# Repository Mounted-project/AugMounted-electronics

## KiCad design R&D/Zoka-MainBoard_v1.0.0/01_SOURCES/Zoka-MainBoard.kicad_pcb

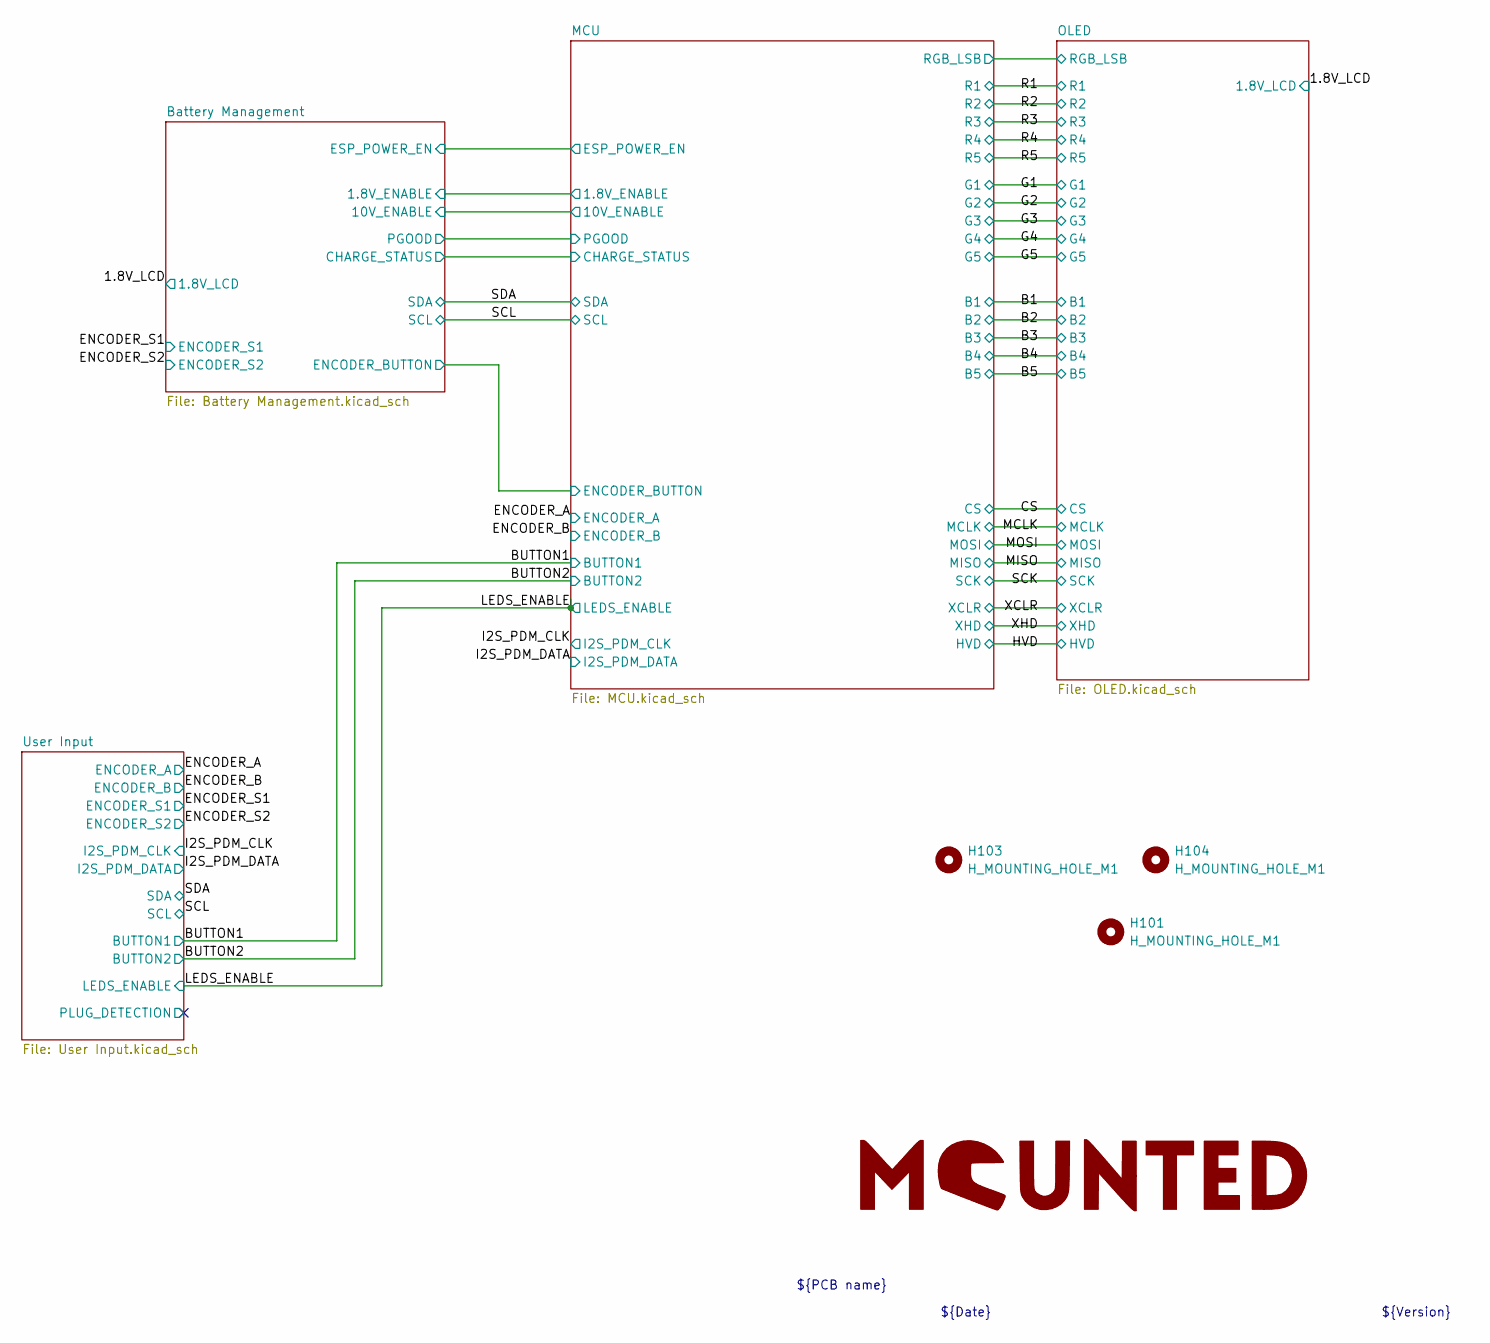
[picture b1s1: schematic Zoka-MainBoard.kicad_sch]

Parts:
H101, H103, H104: H_MOUNTING_HOLE_M1; MountingHole_1.2mm_M1
LOGO101: mounted_logo

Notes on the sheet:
${PCB name}
${Date}
${Version}

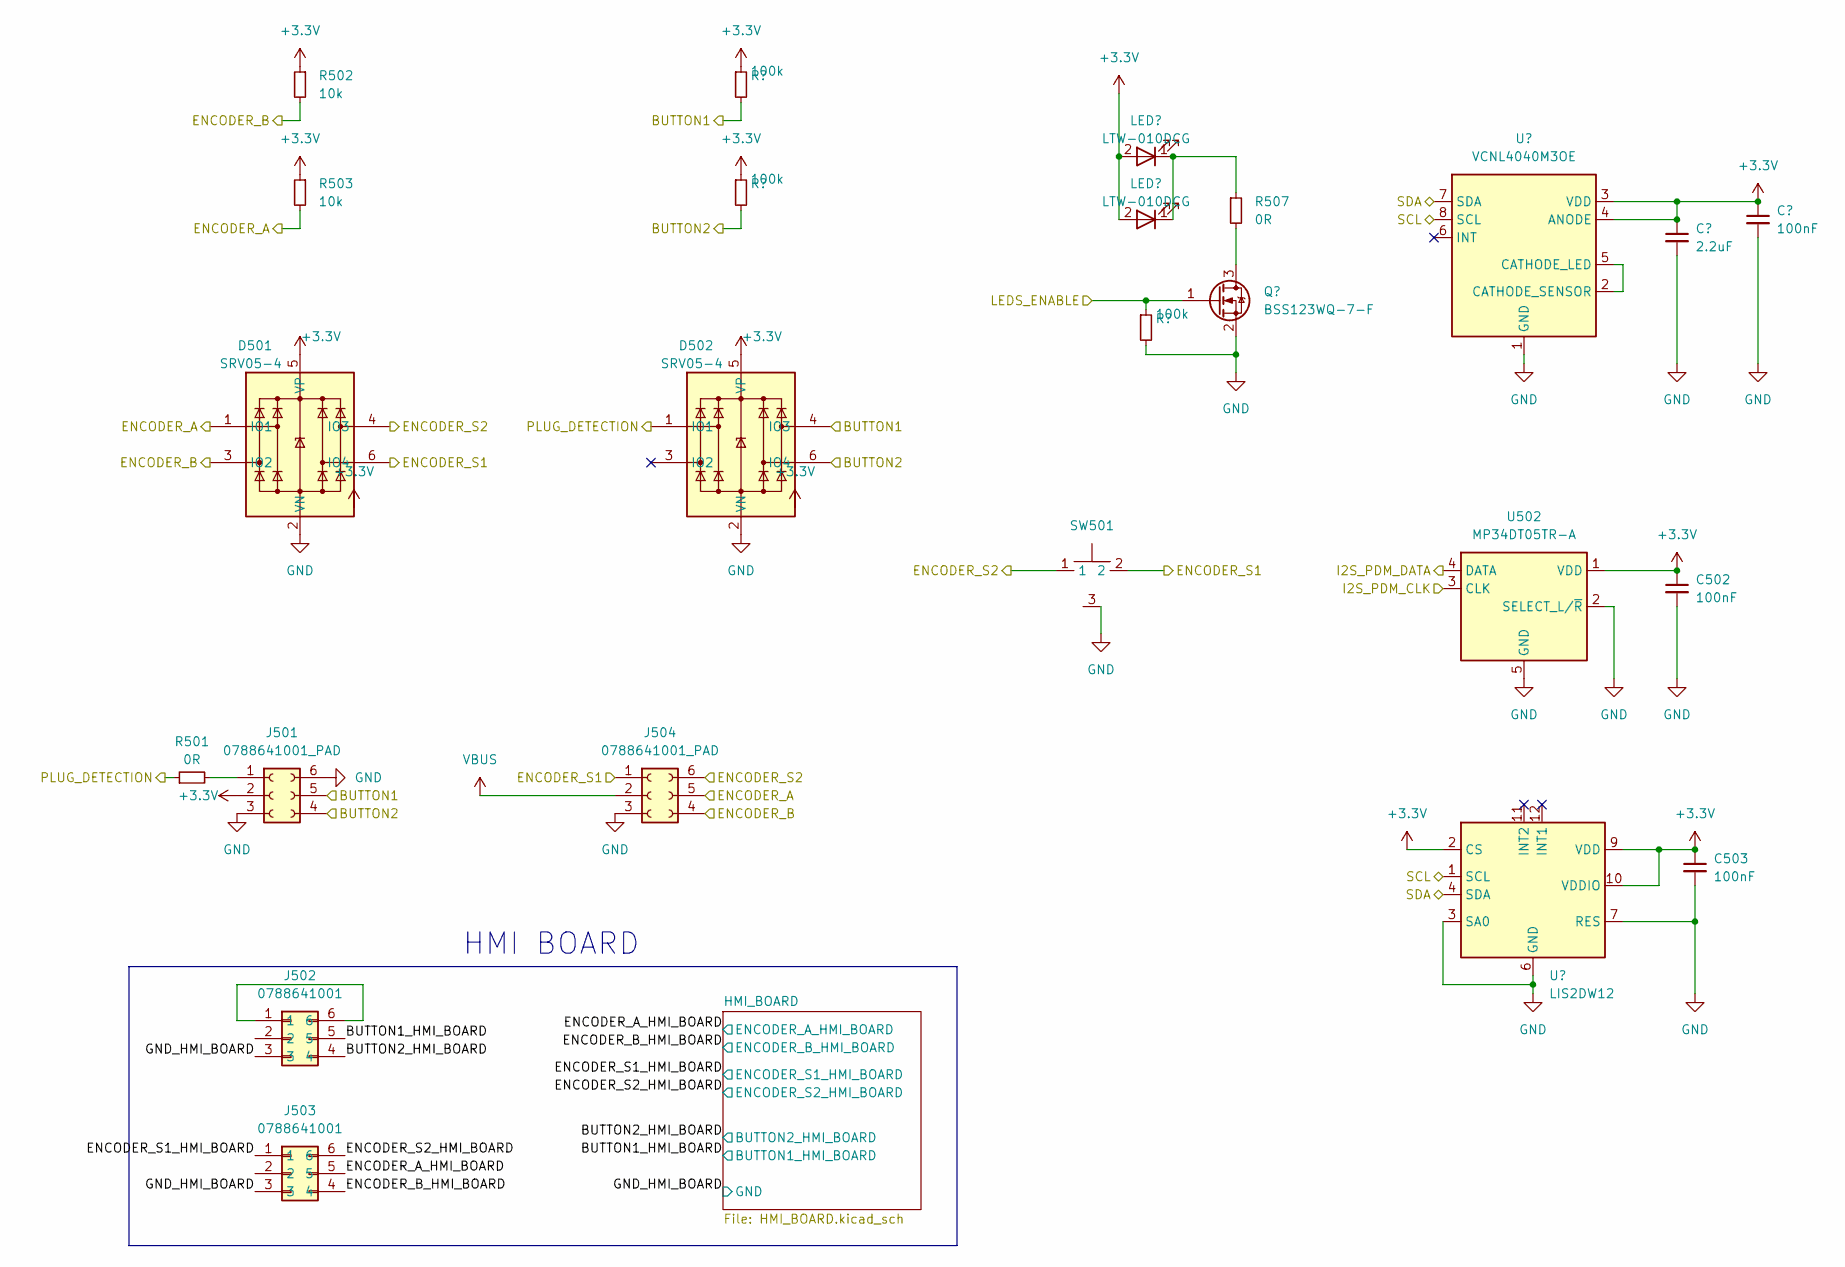
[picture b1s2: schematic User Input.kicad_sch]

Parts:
C501: C_0603_2.2uF_10V_X7R_10%; C_0603_1608Metric; Voltage 10V; Tolerance 10%
C502, C503, C504: C_0603_100nF_100V_X7R_10%; C_0402_1005Metric; Voltage 50V; Tolerance 10%
D501, D502: D_SRV05-4; SOT-23-6_TECH_PUBLIC; MPN SRV05-4
J501, J504: J_0788641001_PAD; J_788641001_PAD; MPN 0788641001
J502, J503: J_0788641001; J_788641001; MPN 0788641001
LED502, LED503: LED_LTW-010DCG; MPN LTW-010DCG
Q501: Q_BSS123WQ-7-F; SOT-323_SC-70_DIODES_INC; MPN BSS123WQ-7-F
R501, R507: R_0402_0R_1%_0.06W; R_0402_1005Metric; Tolerance 1%
R502, R503: R_0603_10k_1%_0.1W; R_0402_1005Metric; Tolerance 1%
R504, R505, R506: R_0402_100k_1%_0.06W; R_0402_1005Metric; Tolerance 1%
SW501: SW_SKRTLAE010; MPN SKRTLAE010
U501: U_VCNL4040M3OE; VCNL4040_4X2X1.1_VISHAY; MPN VCNL4040M3OE
U502: MP34DT05TR-A; U_MP34DT05TR-A; MPN MP34DT05TR-A
U503: LIS2DW12; LGA-12_2x2mm_P0.5mm; MPN LIS2DW12

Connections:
+3.3V: C501.1, C502.1, C503.1, C504.1, D501.5 (VP), D502.5 (VP), J501.2, LED502.2 (A), LED503.2 (A), R502.1, R503.1, R504.1, R505.1, U501.3 (VDD), U501.4 (ANODE), U502.1 (VDD), U503.2 (CS), U503.9 (VDD), U503.10 (VDDIO); also elsewhere on the board
/BUTTON1: D502.4 (IO3), J501.5, R504.2; also elsewhere on the board
/BUTTON2: D502.6 (IO4), J501.4, R505.2; also elsewhere on the board
/ENCODER_A: D501.1 (IO1), J504.5, R503.2; also elsewhere on the board
/ENCODER_B: D501.3 (IO2), J504.4, R502.2; also elsewhere on the board
/ENCODER_S1: D501.6 (IO4), J504.1, SW501.2; also elsewhere on the board
/ENCODER_S2: D501.4 (IO3), J504.6, SW501.1; also elsewhere on the board
/I2S_PDM_CLK: U502.3 (CLK); also elsewhere on the board
/I2S_PDM_DATA: U502.4 (DATA); also elsewhere on the board
/LEDS_ENABLE: Q501.1 (G), R506.1; also elsewhere on the board
/SCL: U501.8 (SCL), U503.1 (SCL); also elsewhere on the board
/SDA: U501.7 (SDA), U503.4 (SDA); also elsewhere on the board
/User Input/PLUG_DETECTION: D502.1 (IO1), R501.1
GND: C501.2, C502.2, C503.2, C504.2, D501.2 (VN), D502.2 (VN), J501.3, J501.6, J504.3, Q501.2 (S), R506.2, SW501.3, U501.1 (GND), U502.2 (SELECT_L/~R), U502.5 (GND), U503.3 (SA0), U503.6 (GND), U503.7 (RES), U503.8 (GND); also elsewhere on the board
unnamed: J501.1, R501.2
unnamed: J502.1, J502.6
unnamed: J502.3, J503.3
unnamed: LED502.1 (K), LED503.1 (K), R507.1
unnamed: Q501.3 (D), R507.2
unnamed: U501.2 (CATHODE_SENSOR), U501.5 (CATHODE_LED)
VBUS: J504.2; also elsewhere on the board

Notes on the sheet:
HMI BOARD

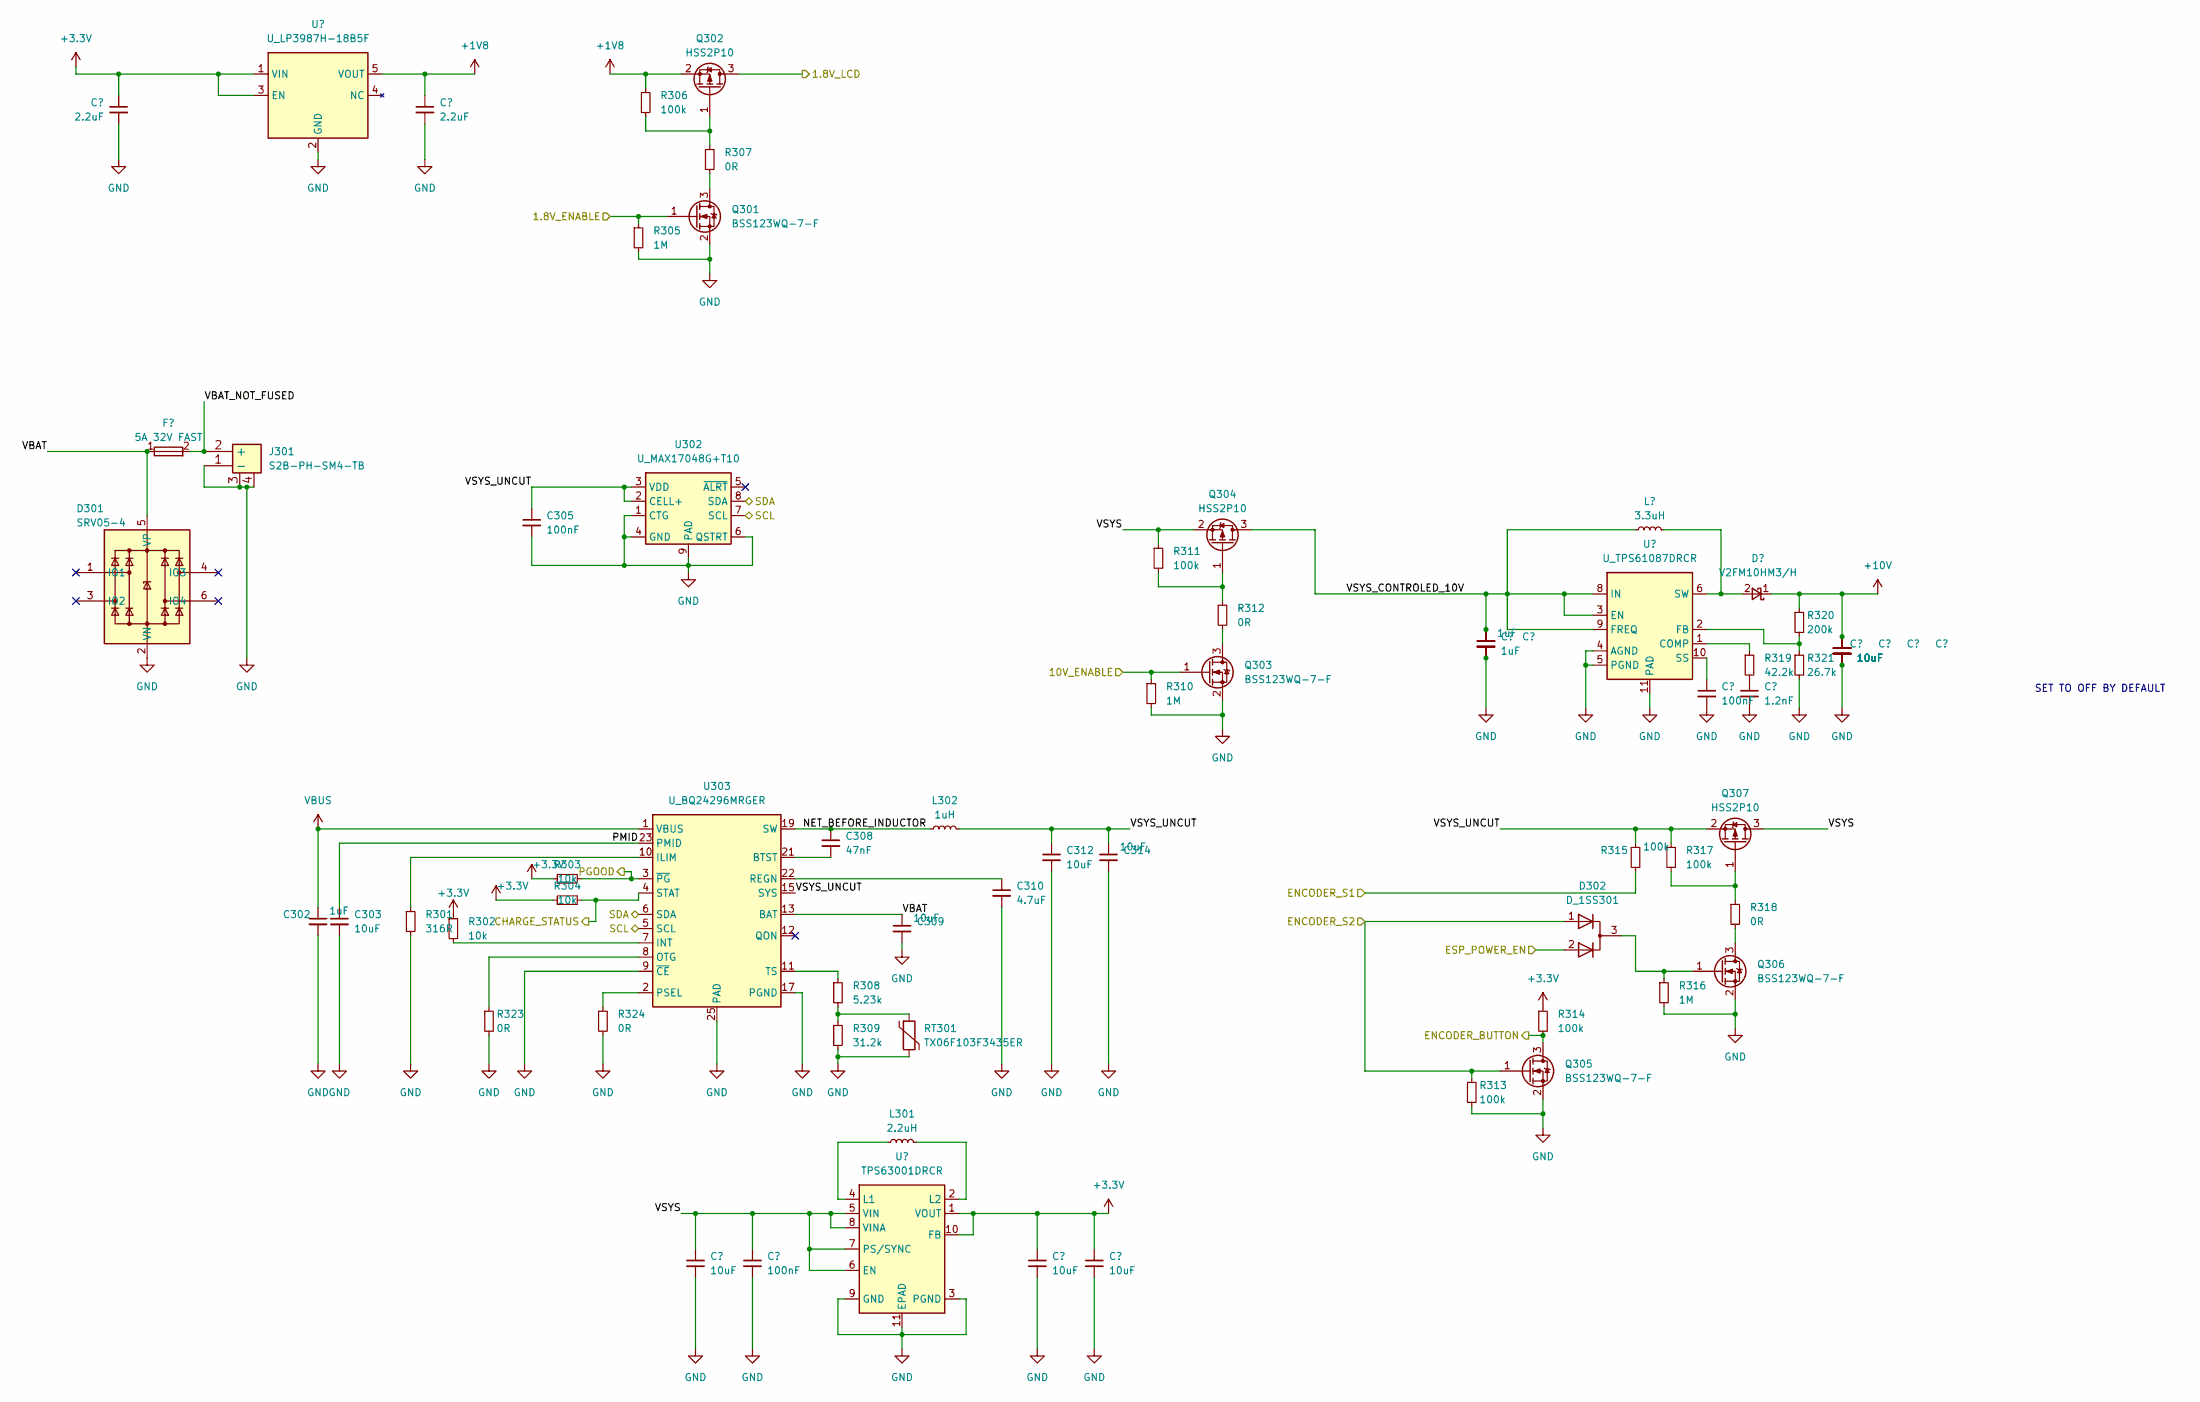
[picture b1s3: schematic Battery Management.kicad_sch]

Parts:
C301, C304: C_0805_2.2uF_25V_X7R_20%; C_0805_1608Metric; Voltage 25V; Tolerance 20%
C302, C315, C316: C_0402_1uF_10V_X7R_10%; C_0402_1005Metric; Voltage 10V; Tolerance 10%
C303, C306, C309, C311, C312, C313, C314: C_0805_10uF_10V_X7R_10%; C_0805_1608Metric; Voltage 25V; Tolerance 10%
C305, C307, C317: C_0603_100nF_100V_X7R_10%; C_0402_1005Metric; Voltage 50V; Tolerance 10%
C308: C_0402_47nF_50V_X7R_10%; C_0402_1005Metric; Voltage 50V; Tolerance 10%
C310: C_0603_4.7uF_16V_X7R_10%; C_0603_1608Metric; Voltage 16V; Tolerance 10%
C318: C_0402_1.2nF_50V_X7R_10%; C_0402_1005Metric; Voltage 50V; Tolerance 10%
C319, C320, C321, C322: C_1206_10uF_25V_X7R_10%; C_0805_1608Metric; Voltage 25V; Tolerance 10%; PartStatus ___PartStatus
D301: D_SRV05-4; SOT-23-6_TECH_PUBLIC; MPN SRV05-4
D302: D_1SS301; SOT-23_TOSHIBA; MPN 1SS301,LF
D303: D_V2FM10HM3/H; D_SMF_VISHAY; MPN V2FM10HM3/H
F301: F_MFU0603FF05000P100; R_0603_1608Metric; MPN MFU0603FF05000P100
J301: J_JST_S2B-PH-SM4-TB; MPN S2B-PH-SM4-TB
L301: L_FNR3015S2R2MT; Tolerance 20%; MPN FNR3015S2R2MT
L302: L_TFM252012ALMA1R0MTAA; TFM252012ALMA1R0MTAA; MPN TFM252012ALMA1R0MTAA
L303: L_7447789003; Tolerance 20%; MPN 7447789003
Q301, Q303, Q305, Q306: Q_BSS123WQ-7-F; SOT-323_SC-70_DIODES_INC; MPN BSS123WQ-7-F
Q302, Q304, Q307: Q_HSS2P10; SOT-23-3_HUASHUO; MPN HSS2P10
R301: R_0402_316R_1%_0.06W; R_0402_1005Metric; Tolerance 1%
R302, R303, R304: R_0402_10k_1%_0.06W; R_0402_1005Metric; Tolerance 1%
R305, R310, R316: R_0603_1M_1%_0.1W; R_0402_1005Metric; Tolerance 1%
R306, R311, R313, R314, R315, R317: R_0402_100k_1%_0.06W; R_0402_1005Metric; Tolerance 1%
R307, R312, R318, R323, R324: R_0402_0R_1%_0.06W; R_0402_1005Metric; Tolerance 1%
R308: R_0402_5.23k_1%_0.06W; R_0402_1005Metric; Tolerance 1%
R309: R_0603_31.2k_0.5%_0.1W; R_0603_1608Metric; Tolerance 0.5%
R319: R_0402_42.2k_1%_0.06W; R_0402_1005Metric; Tolerance 1%
R320: R_0402_200k_1%_0.06W; R_0402_1005Metric; Tolerance 1%; PartStatus ___PartStatus
R321: R_0402_26.7k_1%_0.06W; R_0402_1005Metric; Tolerance 1%; PartStatus ___PartStatus
RT301: RT_TX06F103F3435ER; NTCG16_XXX_TDK; Tolerance 1%; MPN TX06F103F3435ER
U301: U_LP3987H-18B5F; SOT-23-5_LOW_POWER; MPN LP3987H-18B5F
U302: U_MAX17048G+T10; TDFN-8_MAXIM_INTEGRATED; MPN MAX17048G+T10
U303: U_BQ24296MRGER; VQFN-24_TEXAS_INSTRUMENTS; MPN BQ24296MRGER
U304: U_TPS63001DRCR; PVSON-N10_TEXAS_INSTRUMENTS; MPN TPS63001DRCR
U305: U_TPS61087DRCR; PVSON-N10_TEXAS_INSTRUMENTS; MPN TPS61087DRCR

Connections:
+1V8: C304.1, Q302.2 (S), R306.1, U301.5 (VOUT); also elsewhere on the board
+3.3V: C301.1, C311.1, C313.1, R302.1, R303.1, R304.1, R314.1, U301.1 (VIN), U301.3 (EN), U304.1 (VOUT), U304.10 (FB); also elsewhere on the board
+10V: C319.1, C320.1, C321.1, C322.1, D303.1 (K), R320.1; also elsewhere on the board
/1.8V_LCD: Q302.3 (D); also elsewhere on the board
/Battery Management/1.8V_ENABLE: Q301.1 (G), R305.1; also elsewhere on the board
/Battery Management/10V_ENABLE: Q303.1 (G), R310.1; also elsewhere on the board
/Battery Management/CHARGE_STATUS: R304.2, U303.4 (STAT); also elsewhere on the board
/Battery Management/ENCODER_BUTTON: Q305.3 (D), R314.2; also elsewhere on the board
/Battery Management/ESP_POWER_EN: D302.2 (A2); also elsewhere on the board
/Battery Management/NET_BEFORE_INDUCTOR: C308.1, L302.1, U303.19 (SW), U303.20 (SW)
/Battery Management/PGOOD: R303.2, U303.3 (~PG); also elsewhere on the board
/Battery Management/PMID: C303.1, U303.23 (PMID)
/Battery Management/VBAT: C309.1, D301.5 (VP), F301.1, U303.13 (BAT), U303.14 (BAT)
/Battery Management/VBAT_NOT_FUSED: F301.2, J301.2 (+)
/Battery Management/VSYS: C306.1, C307.1, Q304.2 (S), Q307.3 (D), R311.1, U304.5 (VIN), U304.6 (EN), U304.7 (PS/SYNC), U304.8 (VINA)
/Battery Management/VSYS_CONTROLED_10V: C315.1, C316.1, L303.1, Q304.3 (D), U305.3 (EN), U305.8 (IN), U305.9 (FREQ)
/Battery Management/VSYS_UNCUT: C305.1, C312.1, C314.1, L302.2, Q307.2 (S), R315.1, R317.1, U302.2 (CELL+), U302.3 (VDD), U303.15 (SYS), U303.16 (SYS)
/ENCODER_S1: R315.2; also elsewhere on the board
/ENCODER_S2: D302.1 (A1), Q305.1 (G), R313.1; also elsewhere on the board
/SCL: U302.7 (SCL), U303.5 (SCL); also elsewhere on the board
/SDA: U302.8 (SDA), U303.6 (SDA); also elsewhere on the board
GND: C301.2, C302.2, C303.2, C304.2, C305.2, C306.2, C307.2, C309.2, C310.2, C311.2, C312.2, C313.2, C314.2, C315.2, C316.2, C317.2, C318.2, C319.2, C320.2, C321.2, C322.2, D301.2 (VN), J301.1 (-), J301.3, J301.4, Q301.2 (S), Q303.2 (S), Q305.2 (S), Q306.2 (S), R301.2, R305.2, R309.2, R310.2, R313.2, R316.2, R321.2, R323.2, R324.2, RT301.2, U301.2 (GND), U302.1 (CTG), U302.4 (GND), U302.6 (QSTRT), U302.9 (PAD), U303.9 (~CE), U303.17 (PGND), U303.18 (PGND), U303.25 (PAD), U304.3 (PGND), U304.9 (GND), U304.11 (EPAD), U305.4 (AGND), U305.5 (PGND), U305.11 (PAD); also elsewhere on the board
unnamed: C318.1, R319.2
unnamed: D302.3 (K), Q306.1 (G), R316.1
unnamed: D303.2 (A), L303.2, U305.6 (SW), U305.7 (SW)
unnamed: Q301.3 (D), R307.2
unnamed: Q302.1 (G), R306.2, R307.1
unnamed: Q303.3 (D), R312.2
unnamed: Q304.1 (G), R311.2, R312.1
unnamed: Q306.3 (D), R318.2
unnamed: Q307.1 (G), R317.2, R318.1
unnamed: R308.2, R309.1, RT301.1
unnamed: C308.2, U303.21 (BTST)
unnamed: R301.1, U303.10 (ILIM)
unnamed: R302.2, U303.7 (INT)
unnamed: R323.1, U303.8 (OTG)
unnamed: R324.1, U303.2 (PSEL)
unnamed: C310.1, U303.22 (REGN)
unnamed: R308.1, U303.11 (TS)
unnamed: L301.1, U304.4 (L1)
unnamed: L301.2, U304.2 (L2)
unnamed: R319.1, U305.1 (COMP)
unnamed: R320.2, R321.1, U305.2 (FB)
unnamed: C317.1, U305.10 (SS)
VBUS: C302.1, U303.1 (VBUS), U303.24 (VBUS); also elsewhere on the board

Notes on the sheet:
SET TO OFF BY DEFAULT

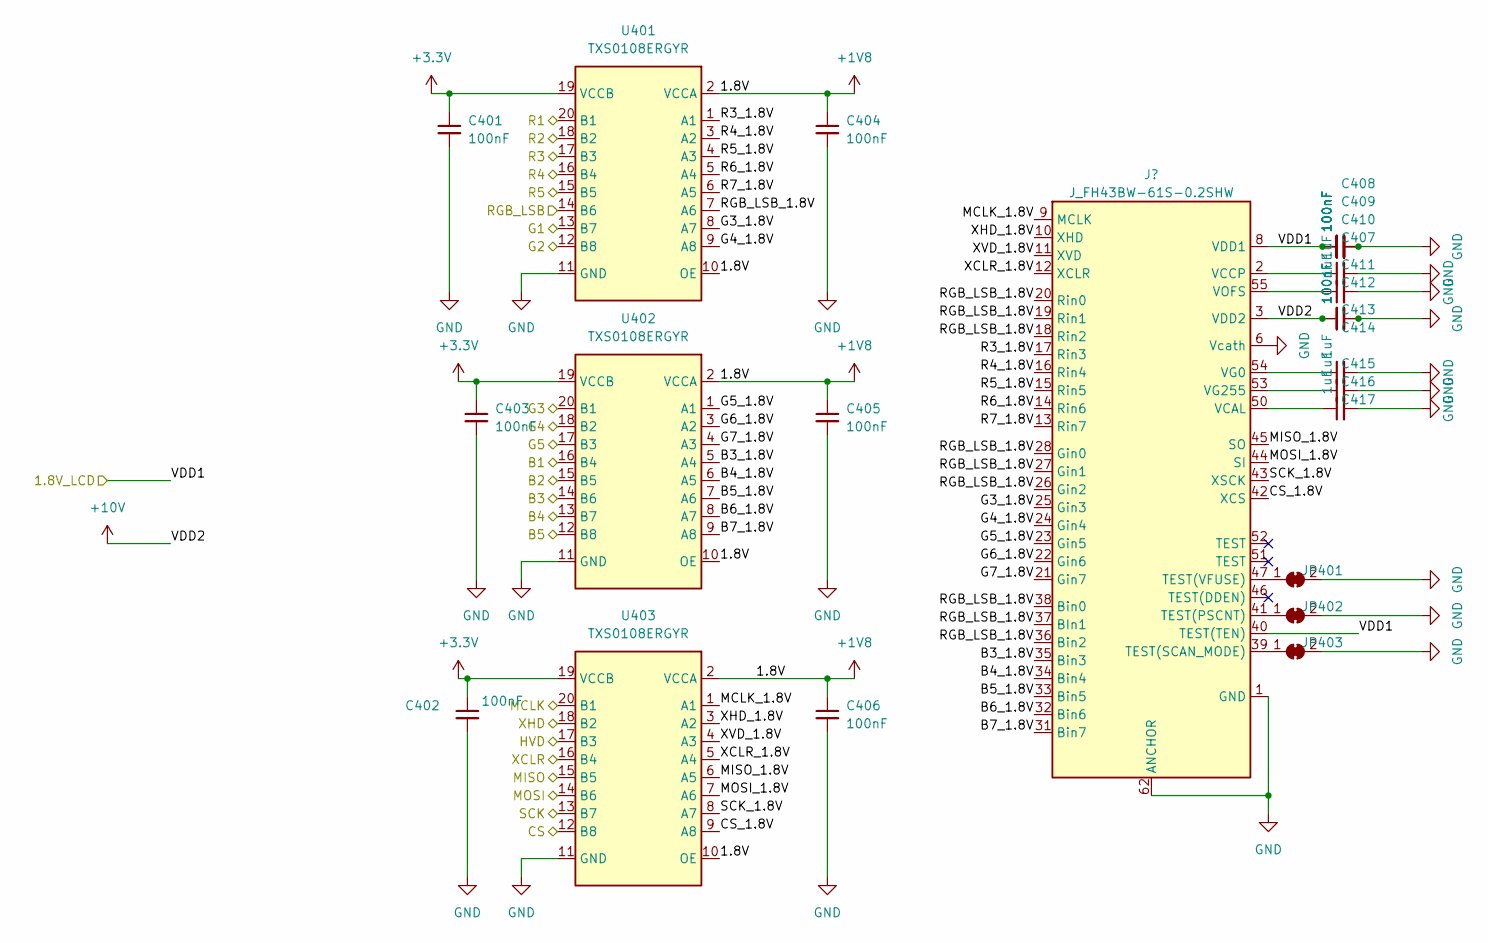
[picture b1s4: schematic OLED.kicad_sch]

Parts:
C401, C402, C403, C404, C405, C406, C407, C408, C409, C410, C413, C414: C_0603_100nF_100V_X7R_10%; C_0402_1005Metric; Voltage 50V; Tolerance 10%
C411, C412, C415, C416, C417: C_0402_1uF_10V_X7R_10%; C_0402_1005Metric; Voltage 10V; Tolerance 10%
J401: J_FH43BW-61S-0.2SHW; MPN FH43BW-61S-0.2SHW
JP401, JP402, JP403: SolderJumper_2_Bridged; SolderJumper-2_P1.3mm_Bridged_RoundedPad1.0x1.5mm
U401, U402, U403: U_TXS0108E; VQFN-20_TEXAS_INSTRUMENTS; MPN TXS0108ERGYR

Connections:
+1V8: C404.1, C405.1, C406.1, U401.2 (VCCA), U401.10 (OE), U402.2 (VCCA), U402.10 (OE), U403.2 (VCCA), U403.10 (OE); also elsewhere on the board
+3.3V: C401.1, C402.1, C403.1, U401.19 (VCCB), U402.19 (VCCB), U403.19 (VCCB); also elsewhere on the board
+10V: C413.1, C414.1, J401.3 (VDD2), J401.59 (VDD2); also elsewhere on the board
/1.8V_LCD: C407.1, C408.1, C409.1, C410.1, J401.8 (VDD1), J401.29 (VDD1), J401.40 (TEST(TEN)), J401.49 (VDD1); also elsewhere on the board
/B1: U402.16 (B4); also elsewhere on the board
/B2: U402.15 (B5); also elsewhere on the board
/B3: U402.14 (B6); also elsewhere on the board
/B4: U402.13 (B7); also elsewhere on the board
/B5: U402.12 (B8); also elsewhere on the board
/CS: U403.12 (B8); also elsewhere on the board
/G1: U401.13 (B7); also elsewhere on the board
/G2: U401.12 (B8); also elsewhere on the board
/G3: U402.20 (B1); also elsewhere on the board
/G4: U402.18 (B2); also elsewhere on the board
/G5: U402.17 (B3); also elsewhere on the board
/HVD: U403.17 (B3); also elsewhere on the board
/MCLK: U403.20 (B1); also elsewhere on the board
/MCU/RGB_LSB: U401.14 (B6); also elsewhere on the board
/MISO: U403.15 (B5); also elsewhere on the board
/MOSI: U403.14 (B6); also elsewhere on the board
/OLED/B3_1.8V: J401.35 (Bin3), U402.5 (A4)
/OLED/B4_1.8V: J401.34 (Bin4), U402.6 (A5)
/OLED/B5_1.8V: J401.33 (Bin5), U402.7 (A6)
/OLED/B6_1.8V: J401.32 (Bin6), U402.8 (A7)
/OLED/B7_1.8V: J401.31 (Bin7), U402.9 (A8)
/OLED/CS_1.8V: J401.42 (XCS), U403.9 (A8)
/OLED/G3_1.8V: J401.25 (Gin3), U401.8 (A7)
/OLED/G4_1.8V: J401.24 (Gin4), U401.9 (A8)
/OLED/G5_1.8V: J401.23 (Gin5), U402.1 (A1)
/OLED/G6_1.8V: J401.22 (Gin6), U402.3 (A2)
/OLED/G7_1.8V: J401.21 (Gin7), U402.4 (A3)
/OLED/MCLK_1.8V: J401.9 (MCLK), U403.1 (A1)
/OLED/MISO_1.8V: J401.45 (SO), U403.6 (A5)
/OLED/MOSI_1.8V: J401.44 (SI), U403.7 (A6)
/OLED/R3_1.8V: J401.17 (Rin3), U401.1 (A1)
/OLED/R4_1.8V: J401.16 (Rin4), U401.3 (A2)
/OLED/R5_1.8V: J401.15 (Rin5), U401.4 (A3)
/OLED/R6_1.8V: J401.14 (Rin6), U401.5 (A4)
/OLED/R7_1.8V: J401.13 (Rin7), U401.6 (A5)
/OLED/RGB_LSB_1.8V: J401.18 (Rin2), J401.19 (Rin1), J401.20 (Rin0), J401.26 (Gin2), J401.27 (Gin1), J401.28 (Gin0), J401.36 (Bin2), J401.37 (BIn1), J401.38 (Bin0), U401.7 (A6)
/OLED/SCK_1.8V: J401.43 (XSCK), U403.8 (A7)
/OLED/XCLR_1.8V: J401.12 (XCLR), U403.5 (A4)
/OLED/XHD_1.8V: J401.10 (XHD), U403.3 (A2)
/OLED/XVD_1.8V: J401.11 (XVD), U403.4 (A3)
/R1: U401.20 (B1); also elsewhere on the board
/R2: U401.18 (B2); also elsewhere on the board
/R3: U401.17 (B3); also elsewhere on the board
/R4: U401.16 (B4); also elsewhere on the board
/R5: U401.15 (B5); also elsewhere on the board
/SCK: U403.13 (B7); also elsewhere on the board
/XCLR: U403.16 (B4); also elsewhere on the board
/XHD: U403.18 (B2); also elsewhere on the board
GND: C401.2, C402.2, C403.2, C404.2, C405.2, C406.2, C407.2, C408.2, C409.2, C410.2, C411.2, C412.2, C413.2, C414.2, C415.2, C416.2, C417.2, J401.1 (GND), J401.4 (GND), J401.5 (GND), J401.6 (Vcath), J401.7 (GND), J401.30 (GND), J401.48 (GND), J401.56 (Vcath), J401.57 (GND), J401.58 (GND), J401.61 (GND), J401.62 (ANCHOR), J401.63 (ANCHOR), JP401.2 (B), JP402.2 (B), JP403.2 (B), U401.11 (GND), U402.11 (GND), U403.11 (GND); also elsewhere on the board
unnamed: C411.1, J401.2 (VCCP), J401.60 (VCCP)
unnamed: J401.41 (TEST(PSCNT)), JP402.1 (A)
unnamed: J401.39 (TEST(SCAN_MODE)), JP403.1 (A)
unnamed: J401.47 (TEST(VFUSE)), JP401.1 (A)
unnamed: C417.1, J401.50 (VCAL)
unnamed: C415.1, J401.54 (VG0)
unnamed: C416.1, J401.53 (VG255)
unnamed: C412.1, J401.55 (VOFS)

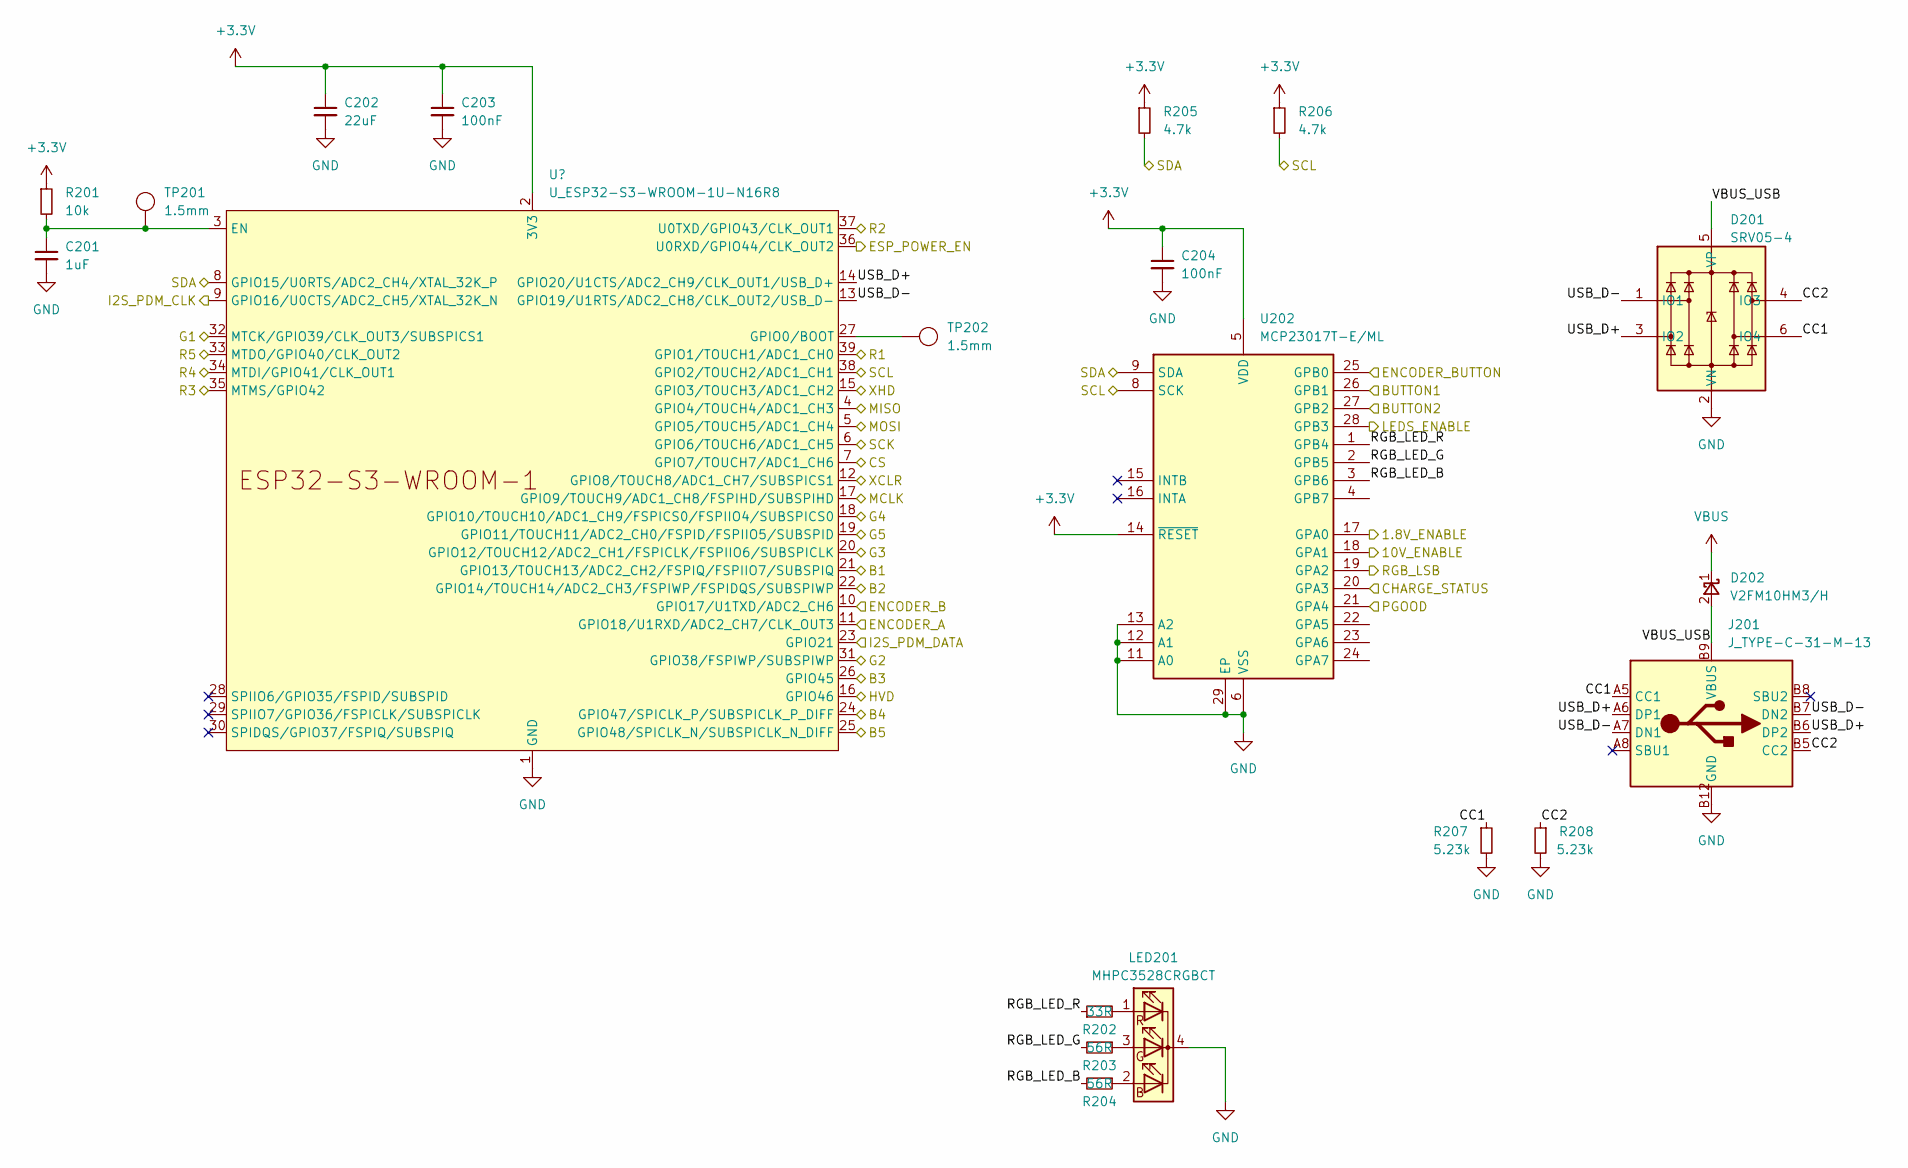
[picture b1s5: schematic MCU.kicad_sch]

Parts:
C201: C_0402_1uF_10V_X7R_10%; C_0402_1005Metric; Voltage 10V; Tolerance 10%
C202: C_0805_22uF_10V_XR7_20%; C_0805_1608Metric; Voltage 10V; Tolerance 20%; PartStatus ___PartStatus
C203, C204: C_0603_100nF_100V_X7R_10%; C_0402_1005Metric; Voltage 50V; Tolerance 10%
D201: D_SRV05-4; SOT-23-6_TECH_PUBLIC; MPN SRV05-4
D202: D_V2FM10HM3/H; D_SMF_VISHAY; MPN V2FM10HM3/H
J201: J_TYPE-C-31-M-13; MPN TYPE-C-31-M-13
LED201: LED_MHPC3528CRGBCT; MPN MHPC3528CRGBCT
R201: R_0603_10k_1%_0.1W; R_0402_1005Metric; Tolerance 1%
R202: R_0402_33R_1%_0.06W; R_0402_1005Metric; Tolerance 1%
R203, R204: R_0402_56R_1%_0.06W; R_0402_1005Metric; Tolerance 1%
R205, R206: R_0603_4.7k_1%_0.1W; R_0402_1005Metric; Tolerance 1%
R207, R208: R_0603_5.23k_1%_0.1W; R_0402_1005Metric; Tolerance 1%
TP201, TP202: TESTPOINT_1.5MM
U201: ESP32-S3-WROOM-1U-N16R8; ESP32-S3-WROOM-1U; MPN ESP32-S3-WROOM-1U-N16R8
U202: U_MCP23017T-E/ML; QFN-28-1EP_6x6mm_P0.65mm_EP4.25x4.25mm_MICROCHIP; MPN MCP23017T-E/ML

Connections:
+3.3V: C202.1, C203.1, C204.1, R201.1, R205.1, R206.1, U201.2 (3V3), U202.5 (VDD), U202.14 (~RESET); also elsewhere on the board
/B1: U201.21 (GPIO13/TOUCH13/ADC2_CH2/FSPIQ/FSPIIO7/S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); also elsewhere on the board
/B2: U201.22 (GPIO14/TOUCH14/ADC2_CH3/FSPIWP/FSPIDQS/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); also elsewhere on the board
/B3: U201.26 (GPIO45); also elsewhere on the board
/B4: U201.24 (GPIO47/SPICLK_P/SUBSPICLK_P_DIFF); also elsewhere on the board
/B5: U201.25 (GPIO48/SPICLK_N/SUBSPICLK_N_DIFF); also elsewhere on the board
/BUTTON1: U202.26 (GPB1); also elsewhere on the board
/BUTTON2: U202.27 (GPB2); also elsewhere on the board
/Battery Management/1.8V_ENABLE: U202.17 (GPA0); also elsewhere on the board
/Battery Management/10V_ENABLE: U202.18 (GPA1); also elsewhere on the board
/Battery Management/CHARGE_STATUS: U202.20 (GPA3); also elsewhere on the board
/Battery Management/ENCODER_BUTTON: U202.25 (GPB0); also elsewhere on the board
/Battery Management/ESP_POWER_EN: U201.36 (U0RXD/GPIO44/CLK_OUT2); also elsewhere on the board
/Battery Management/PGOOD: U202.21 (GPA4); also elsewhere on the board
/CS: U201.7 (GPIO7/TOUCH7/ADC1_CH6); also elsewhere on the board
/ENCODER_A: U201.11 (GPIO18/U1RXD/ADC2_CH7/CLK_OUT3); also elsewhere on the board
/ENCODER_B: U201.10 (GPIO17/U1TXD/ADC2_CH6); also elsewhere on the board
/G1: U201.32 (MTCK/GPIO39/CLK_OUT3/SUBSPICS1); also elsewhere on the board
/G2: U201.31 (GPIO38/FSPIWP/SUBSPIWP); also elsewhere on the board
/G3: U201.20 (GPIO12/TOUCH12/ADC2_CH1/FSPICLK/FSPIIO6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); also elsewhere on the board
/G4: U201.18 (GPIO10/TOUCH10/ADC1_CH9/FSPICS0/FSPIIO4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); also elsewhere on the board
/G5: U201.19 (GPIO11/TOUCH11/ADC2_CH0/FSPID/FSPIIO5/S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); also elsewhere on the board
/HVD: U201.16 (GPIO46); also elsewhere on the board
/I2S_PDM_CLK: U201.9 (GPIO16/U0CTS/ADC2_CH5/XTAL_32K_N); also elsewhere on the board
/I2S_PDM_DATA: U201.23 (GPIO21); also elsewhere on the board
/LEDS_ENABLE: U202.28 (GPB3); also elsewhere on the board
/MCLK: U201.17 (GPIO9/TOUCH9/ADC1_CH8/FSPIHD/SUBSPIHD); also elsewhere on the board
/MCU/CC1: D201.6 (IO4), J201.A5 (CC1), R207.1
/MCU/CC2: D201.4 (IO3), J201.B5 (CC2), R208.1
/MCU/RGB_LED_B: R204.2, U202.3 (GPB6)
/MCU/RGB_LED_G: R203.2, U202.2 (GPB5)
/MCU/RGB_LED_R: R202.1, U202.1 (GPB4)
/MCU/RGB_LSB: U202.19 (GPA2); also elsewhere on the board
/MCU/USB_D+: D201.3 (IO2), J201.A6 (DP1), J201.B6 (DP2), U201.14 (GPIO20/U1CTS/ADC2_CH9/CLK_OUT1/USB_D+)
/MCU/USB_D-: D201.1 (IO1), J201.A7 (DN1), J201.B7 (DN2), U201.13 (GPIO19/U1RTS/ADC2_CH8/CLK_OUT2/USB_D-)
/MCU/VBUS_USB: D201.5 (VP), D202.2 (A), J201.A4 (VBUS), J201.A9 (VBUS), J201.B4 (VBUS), J201.B9 (VBUS)
/MISO: U201.4 (GPIO4/TOUCH4/ADC1_CH3); also elsewhere on the board
/MOSI: U201.5 (GPIO5/TOUCH5/ADC1_CH4); also elsewhere on the board
/R1: U201.39 (GPIO1/TOUCH1/ADC1_CH0); also elsewhere on the board
/R2: U201.37 (U0TXD/GPIO43/CLK_OUT1); also elsewhere on the board
/R3: U201.35 (MTMS/GPIO42); also elsewhere on the board
/R4: U201.34 (MTDI/GPIO41/CLK_OUT1); also elsewhere on the board
/R5: U201.33 (MTDO/GPIO40/CLK_OUT2); also elsewhere on the board
/SCK: U201.6 (GPIO6/TOUCH6/ADC1_CH5); also elsewhere on the board
/SCL: R206.2, U201.38 (GPIO2/TOUCH2/ADC1_CH1), U202.8 (SCK); also elsewhere on the board
/SDA: R205.2, U201.8 (GPIO15/U0RTS/ADC2_CH4/XTAL_32K_P), U202.9 (SDA); also elsewhere on the board
/XCLR: U201.12 (GPIO8/TOUCH8/ADC1_CH7/SUBSPICS1); also elsewhere on the board
/XHD: U201.15 (GPIO3/TOUCH3/ADC1_CH2); also elsewhere on the board
GND: C201.2, C202.2, C203.2, C204.2, D201.2 (VN), J201.A1 (GND), J201.A12 (GND), J201.B1 (GND), J201.B12 (GND), J201.GND, LED201.4 (K), R207.2, R208.2, U201.1 (GND), U201.40 (GND), U201.41 (GND), U202.6 (VSS), U202.11 (A0), U202.12 (A1), U202.13 (A2), U202.29 (EP); also elsewhere on the board
unnamed: LED201.3 (BA), R203.1
unnamed: LED201.2 (GA), R204.1
unnamed: LED201.1 (RA), R202.2
unnamed: C201.1, R201.2, TP201.1, U201.3 (EN)
unnamed: TP202.1, U201.27 (GPIO0/BOOT)
VBUS: D202.1 (K); also elsewhere on the board
